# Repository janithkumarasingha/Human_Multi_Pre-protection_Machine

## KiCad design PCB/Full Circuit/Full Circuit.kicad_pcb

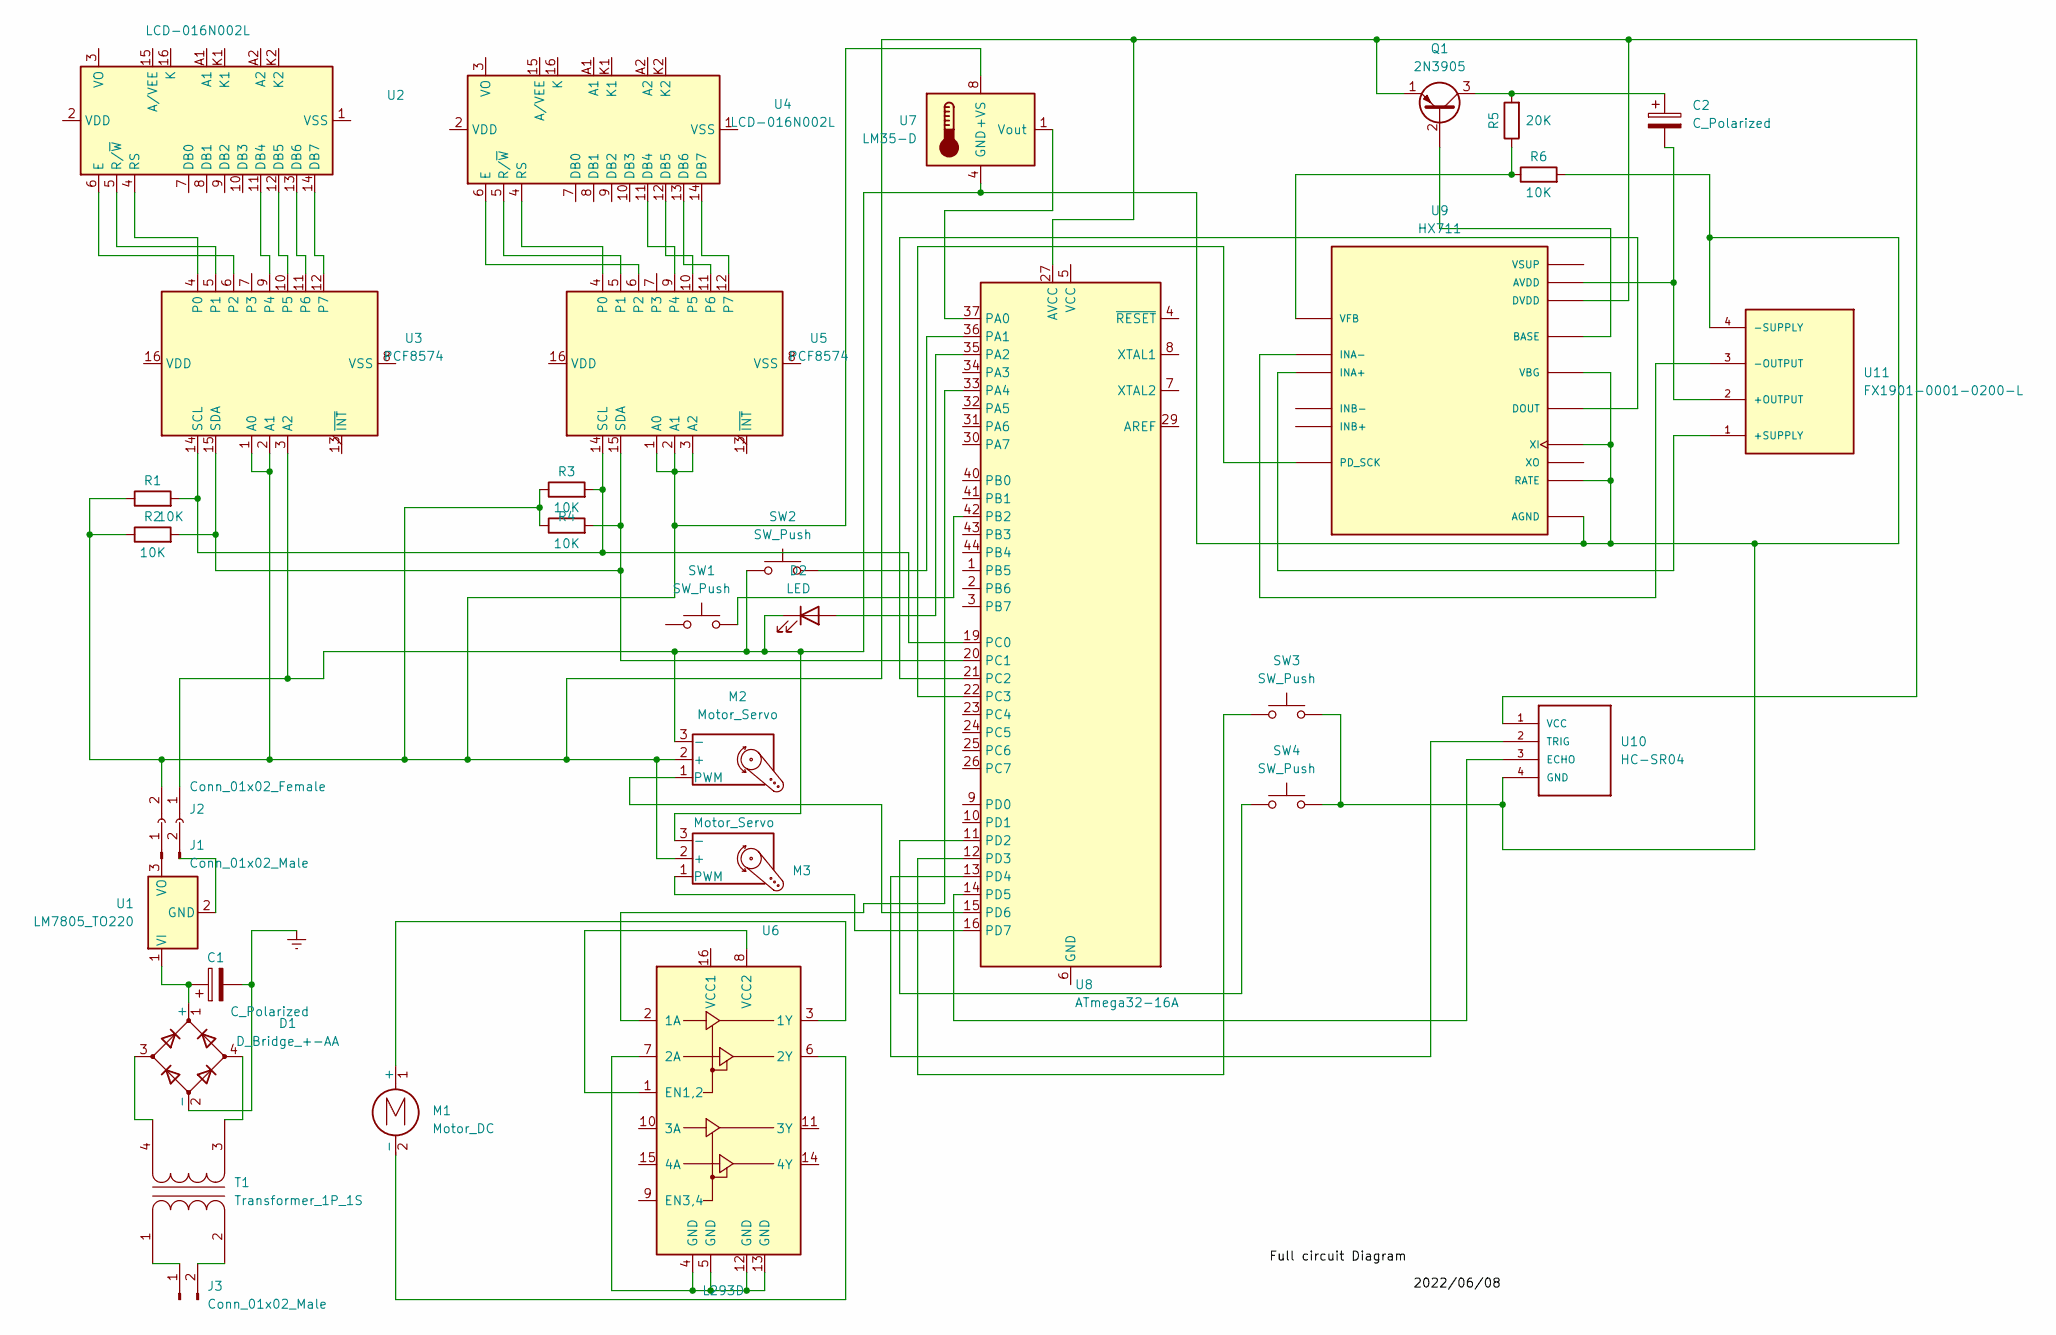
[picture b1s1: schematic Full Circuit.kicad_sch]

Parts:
C1, C2: C_Polarized; CP_Axial_L18.0mm_D10.0mm_P25.00mm_Horizontal
D1: D_Bridge_+-AA; Diode_Bridge_Round_D9.0mm
D2: LED; LED_D5.0mm_Horizontal_O1.27mm_Z3.0mm_IRBlack
J1, J3: Conn_01x02_Male; Stocko_MKS_1651-6-0-202_1x2_P2.50mm_Vertical
J2: Conn_01x02_Female; Stocko_MKS_1652-6-0-202_1x2_P2.50mm_Vertical
M1: Motor_DC; XDCR_C0720B001F
M2, M3: Motor_Servo; TO92254P520H877-3
Q1: 2N3905; TO-92_Inline
R1, R2, R3, R4, R6: 10K; R_Axial_DIN0414_L11.9mm_D4.5mm_P15.24mm_Horizontal
R5: 20K; R_Axial_DIN0414_L11.9mm_D4.5mm_P15.24mm_Horizontal
SW1, SW2, SW3, SW4: SW_Push; SW_PB400EEQX
T1: Transformer_1P_1S; Transformer_37x44
U1: LM7805_TO220; TO-220-3_Vertical
U2, U4: LCD-016N002L
U3, U5: PCF8574; DIP794W45P254L1969H508Q16
U6: L293D; DIP-16_W7.62mm
U7: LM35-D; SOIC-8_3.9x4.9mm_P1.27mm
U8: ATmega32-16A; TQFP-44_10x10mm_P0.8mm
U9: HX711; SOP127P600X180-16N; PARTREV V2.0
U10: HC-SR04; XCVR_HC-SR04
U11: FX1901-0001-0200-L; SENSOR_FX1901-0001-0200-L

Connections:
Earth: C1.2, D1.2 (-)
unnamed: C1.1, D1.1 (+), U1.1 (VI)
unnamed: C2.1, Q1.3 (C), R5.2
unnamed: C2.2, U9.3 (AVDD), U11.2 (+OUTPUT)
unnamed: D1.3, T1.4 (SB)
unnamed: D1.4, T1.3 (SA)
unnamed: D2.1 (K), J2.1, M2.3 (-), M3.3 (-), R6.2, SW2.1, SW3.2, SW4.2, U3.3 (A2), U7.4 (GND), U9.5 (AGND), U9.6 (VBG), U9.14 (XI), U9.15 (RATE), U10.4 (GND), U11.4 (-SUPPLY)
unnamed: D2.2 (A), U8.35 (PA2)
unnamed: J2.2, M2.2 (+), M3.2 (+), Q1.1 (E), R1.1, R2.1, R3.1, R4.1, U3.1 (A0), U3.2 (A1), U5.1 (A0), U5.2 (A1), U5.3 (A2), U7.8 (+VS), U8.27 (AVCC), U9.16 (DVDD), U10.1 (VCC)
unnamed: J3.1, T1.1 (AA)
unnamed: J3.2, T1.2 (AB)
unnamed: M1.1 (+), U6.3 (1Y)
unnamed: M1.2 (-), U6.6 (2Y)
unnamed: M2.1 (PWM), U8.15 (PD6)
unnamed: M3.1 (PWM), U8.16 (PD7)
unnamed: Q1.2 (B), U9.2 (BASE)
unnamed: R1.2, R3.2, U3.14 (SCL), U5.14 (SCL), U8.19 (PC0)
unnamed: R2.2, R4.2, U3.15 (SDA), U5.15 (SDA), U8.20 (PC1)
unnamed: R5.1, R6.1, U9.4 (VFB)
unnamed: SW1.2, U8.42 (PB2)
unnamed: SW2.2, U8.36 (PA1)
unnamed: SW3.1, U8.12 (PD3)
unnamed: SW4.1, U8.11 (PD2)
unnamed: U2.4 (RS), U3.4 (P0)
unnamed: U2.5 (R/~W), U3.5 (P1)
unnamed: U2.6 (E), U3.6 (P2)
unnamed: U2.11 (DB4), U3.9 (P4)
unnamed: U2.12 (DB5), U3.10 (P5)
unnamed: U2.13 (DB6), U3.11 (P6)
unnamed: U2.14 (DB7), U3.12 (P7)
unnamed: U4.4 (RS), U5.4 (P0)
unnamed: U4.5 (R/~W), U5.5 (P1)
unnamed: U4.6 (E), U5.6 (P2)
unnamed: U4.11 (DB4), U5.9 (P4)
unnamed: U4.12 (DB5), U5.10 (P5)
unnamed: U4.13 (DB6), U5.11 (P6)
unnamed: U4.14 (DB7), U5.12 (P7)
unnamed: U6.1 (EN1,2), U6.8 (VCC2)
unnamed: U6.2 (1A), U8.33 (PA4)
unnamed: U6.4 (GND), U6.5 (GND), U6.7 (2A), U6.12 (GND), U6.13 (GND)
unnamed: U7.1 (Vout), U8.37 (PA0)
unnamed: U8.5 (VCC), U8.17 (VCC), U8.38 (VCC)
unnamed: U8.6 (GND), U8.18 (GND), U8.28 (GND), U8.39 (GND)
unnamed: U8.21 (PC2), U9.12 (DOUT)
unnamed: U8.22 (PC3), U9.11 (PD_SCK)
unnamed: U8.13 (PD4), U10.2 (TRIG)
unnamed: U8.14 (PD5), U10.3 (ECHO)
unnamed: U9.8 (INA+), U11.1 (+SUPPLY)
unnamed: U9.7 (INA-), U11.3 (-OUTPUT)

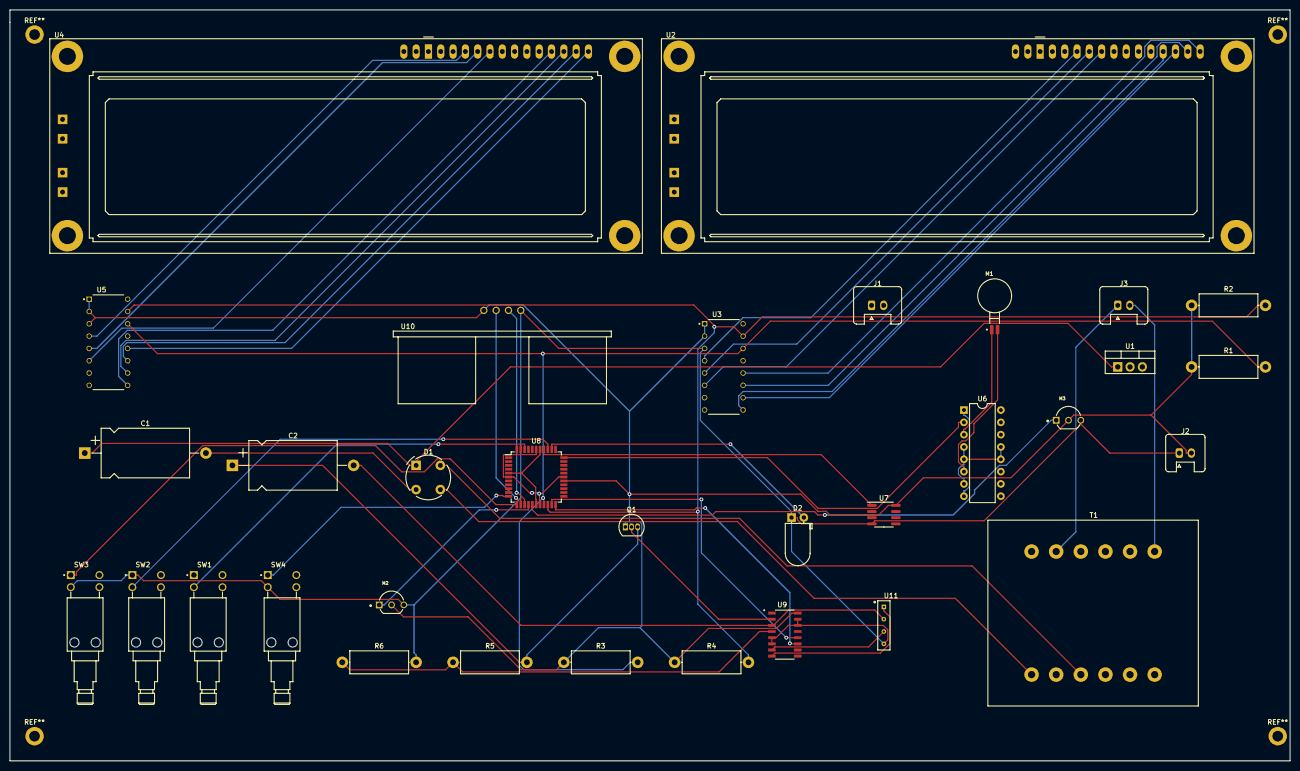
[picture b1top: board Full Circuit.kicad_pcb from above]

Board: 2 copper layers, 264.2 x 154.9 mm, 33 parts (0 on the bottom side), 49 nets.

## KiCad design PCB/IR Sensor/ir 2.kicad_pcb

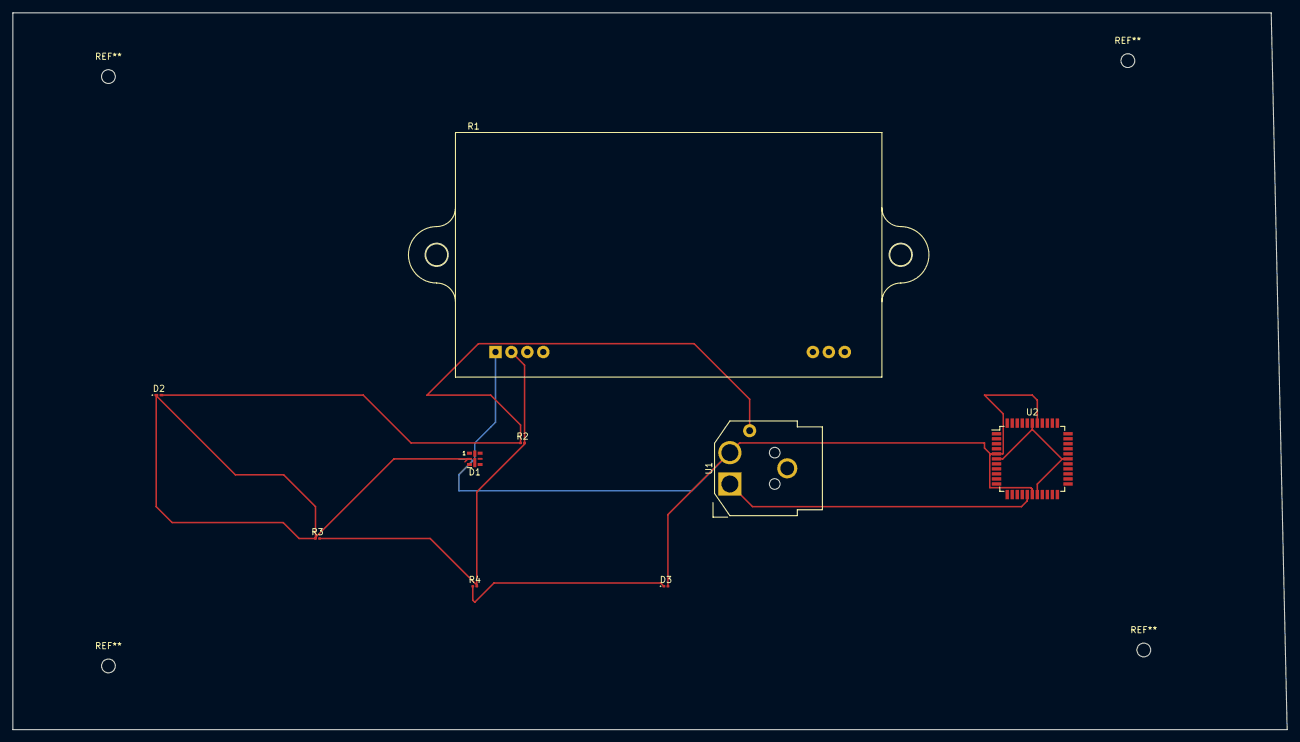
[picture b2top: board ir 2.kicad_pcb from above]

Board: 2 copper layers, 203.2 x 114.3 mm, 9 parts (0 on the bottom side), 7 nets.

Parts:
D1: LED; LED-APA102-2020
D2: D_Photo; D_0201_0603Metric_Pad0.64x0.40mm_HandSolder
D3: D_Photo; D_0201_0603Metric
R1: 150; Reverb_BTDR-1H
R2: 210000; R_0201_0603Metric
R3: 310000; R_0201_0603Metric
R4: 4150; R_0201_0603Metric
U1: LM358; CUI_PD-30
U2: ATmega32-16A; TQFP-44_10x10mm_P0.8mm

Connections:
unnamed: D1.1 (K), R1.1
unnamed: D2.2 (A), R2.1, U1.3 (+)
unnamed: D3.1 (K), R4.1
unnamed: R1.2, R2.2, R3.2, R4.2
unnamed: U1.1, U2.16 (PD7)
unnamed: U2.6 (GND), U2.18 (GND), U2.28 (GND), U2.39 (GND)
VCC: D1.2 (A), D2.1 (K), D3.2 (A), R3.1, U1.2 (-), U2.5 (VCC), U2.17 (VCC), U2.38 (VCC)

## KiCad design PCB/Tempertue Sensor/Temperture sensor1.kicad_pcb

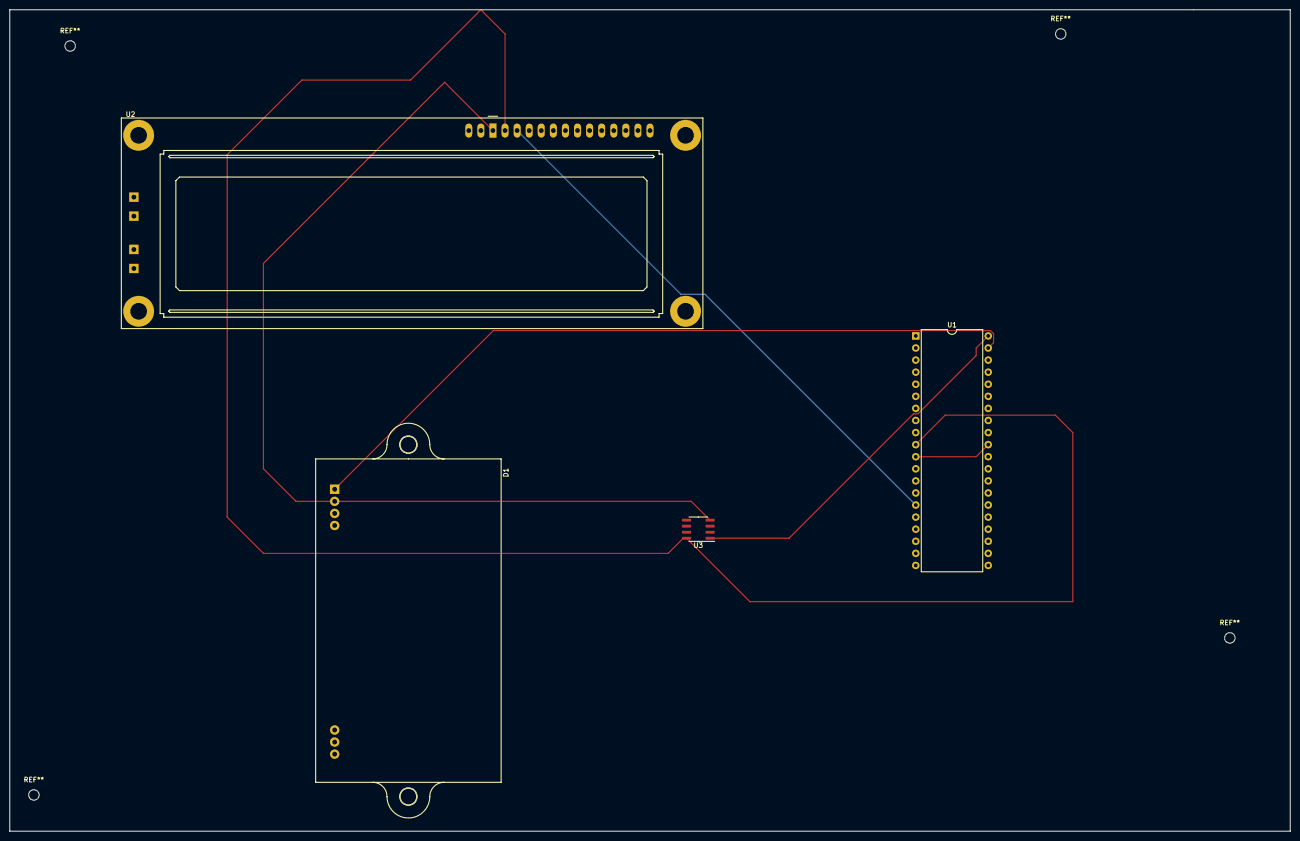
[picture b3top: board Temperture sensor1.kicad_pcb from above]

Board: 2 copper layers, 269.2 x 172.7 mm, 4 parts (0 on the bottom side), 6 nets.

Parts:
D1: LED; Reverb_BTDR-1H
U1: ATmega32A-P; DIP-40_W15.24mm
U2: LCD-016N002L
U3: LM35-D; SOIC-8_3.9x4.9mm_P1.27mm

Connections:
GNDD: D1.2 (A), U2.1 (VSS), U3.4 (GND)
unnamed: D1.1 (K), U1.39 (PA1)
unnamed: U1.11 (GND), U1.31 (GND)
unnamed: U1.15 (PD1), U2.3 (VO)
unnamed: U1.40 (PA0), U3.1 (Vout)
VCC: U1.10 (VCC), U2.2 (VDD), U3.8 (+VS)

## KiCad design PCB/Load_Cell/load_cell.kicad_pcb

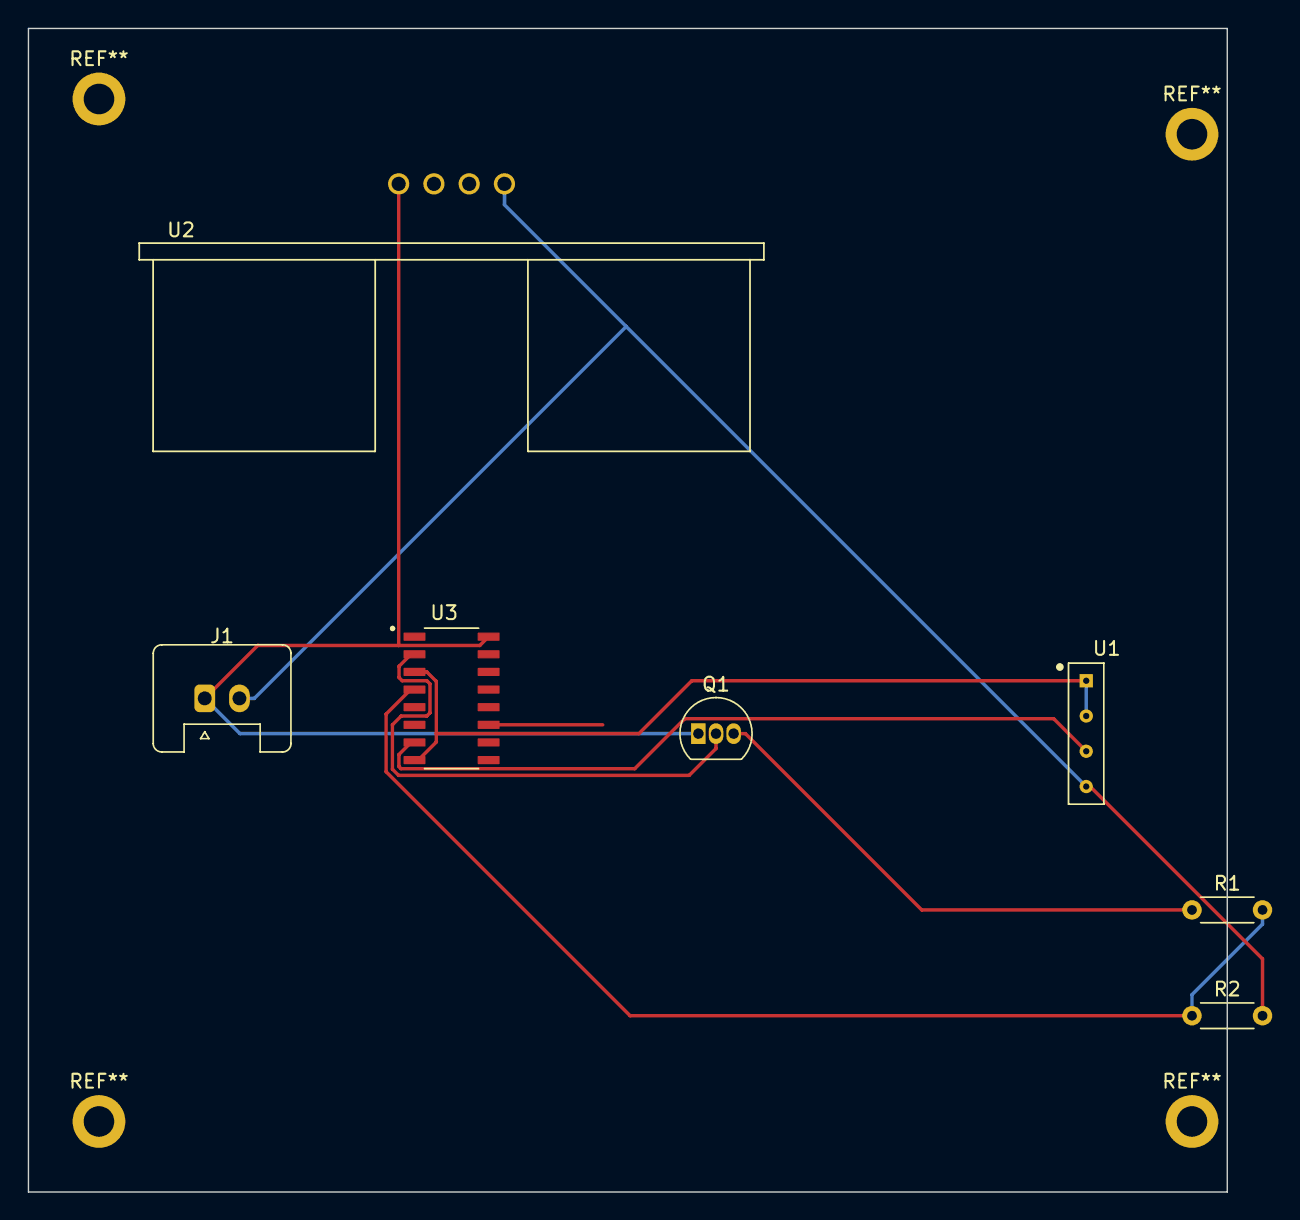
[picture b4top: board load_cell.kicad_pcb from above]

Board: 2 copper layers, 86.4 x 83.8 mm, 7 parts (0 on the bottom side), 7 nets.

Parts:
J1: Conn_01x02_Female; Stocko_MKS_1651-6-0-202_1x2_P2.50mm_Vertical
Q1: 2N3905; TO-92_Inline
R1, R2: R; R_Axial_DIN0204_L3.6mm_D1.6mm_P5.08mm_Horizontal
U1: FX1901-0001-0200-L; SENSOR_FX1901-0001-0200-L
U2: HC-SR04; XCVR_HC-SR04
U3: HX711; SOP127P600X180-16N

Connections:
unnamed: J1.1, Q1.1 (E), U2.1 (VCC), U3.16 (DVDD)
unnamed: J1.2, R2.2, U1.4 (-SUPPLY), U2.4 (GND)
unnamed: Q1.2 (B), U3.2 (BASE)
unnamed: Q1.3 (C), R1.1
unnamed: R1.2, R2.1, U3.4 (VFB)
unnamed: U1.1 (+SUPPLY), U1.2 (+OUTPUT), U3.3 (AVDD), U3.8 (INA+)
unnamed: U1.3 (-OUTPUT), U3.7 (INA-)

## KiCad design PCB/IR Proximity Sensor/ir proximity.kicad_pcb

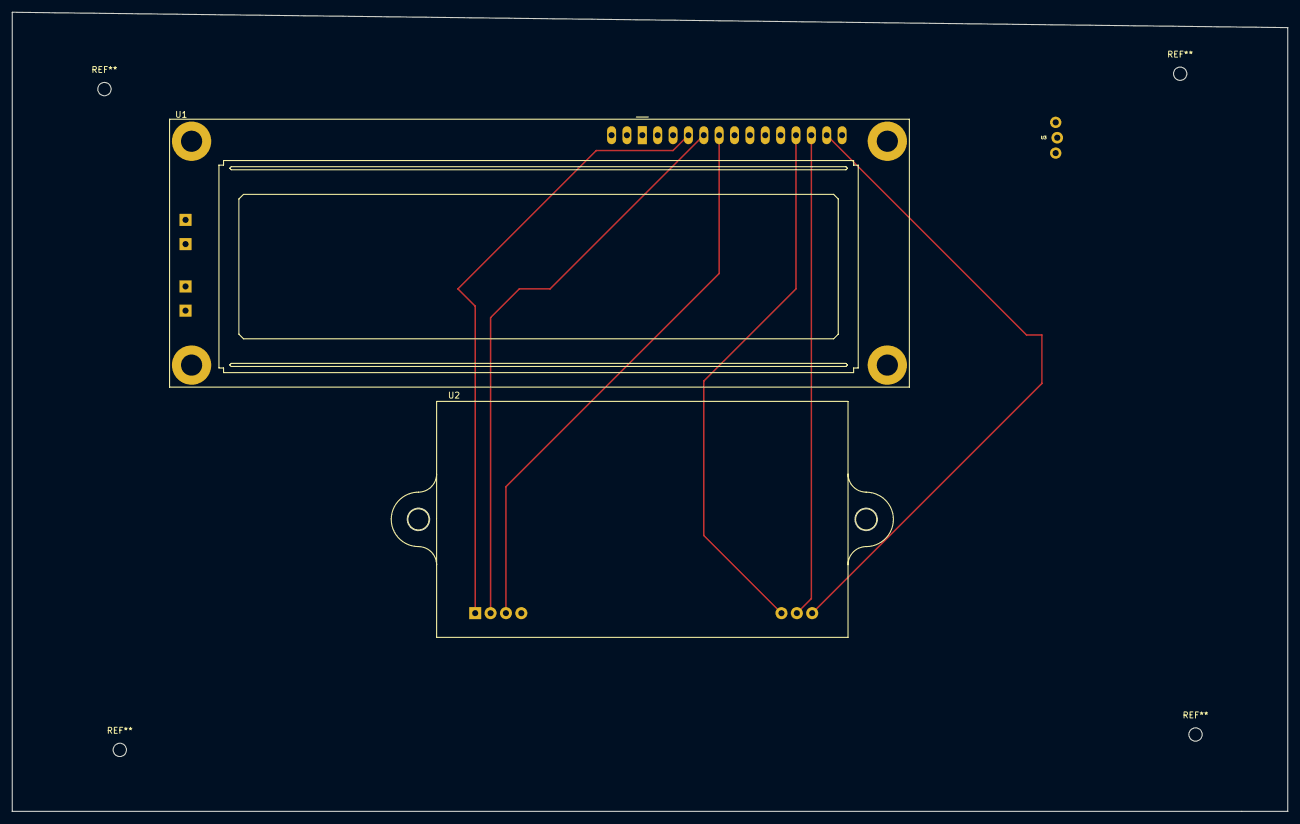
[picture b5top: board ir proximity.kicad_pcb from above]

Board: 2 copper layers, 210.8 x 132.1 mm, 3 parts (0 on the bottom side), 6 nets.

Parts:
U1: LCD-016N002L
U2: ATmega32A-P; Reverb_BTDR-1H
U3: TSSP58038

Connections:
unnamed: U1.4 (RS), U2.1 (PB0)
unnamed: U1.5 (R/~W), U2.2 (PB1)
unnamed: U1.6 (E), U2.3 (PB2)
unnamed: U1.11 (DB4), U2.5 (PB4)
unnamed: U1.12 (DB5), U2.6 (PB5)
unnamed: U1.13 (DB6), U2.7 (PB6)

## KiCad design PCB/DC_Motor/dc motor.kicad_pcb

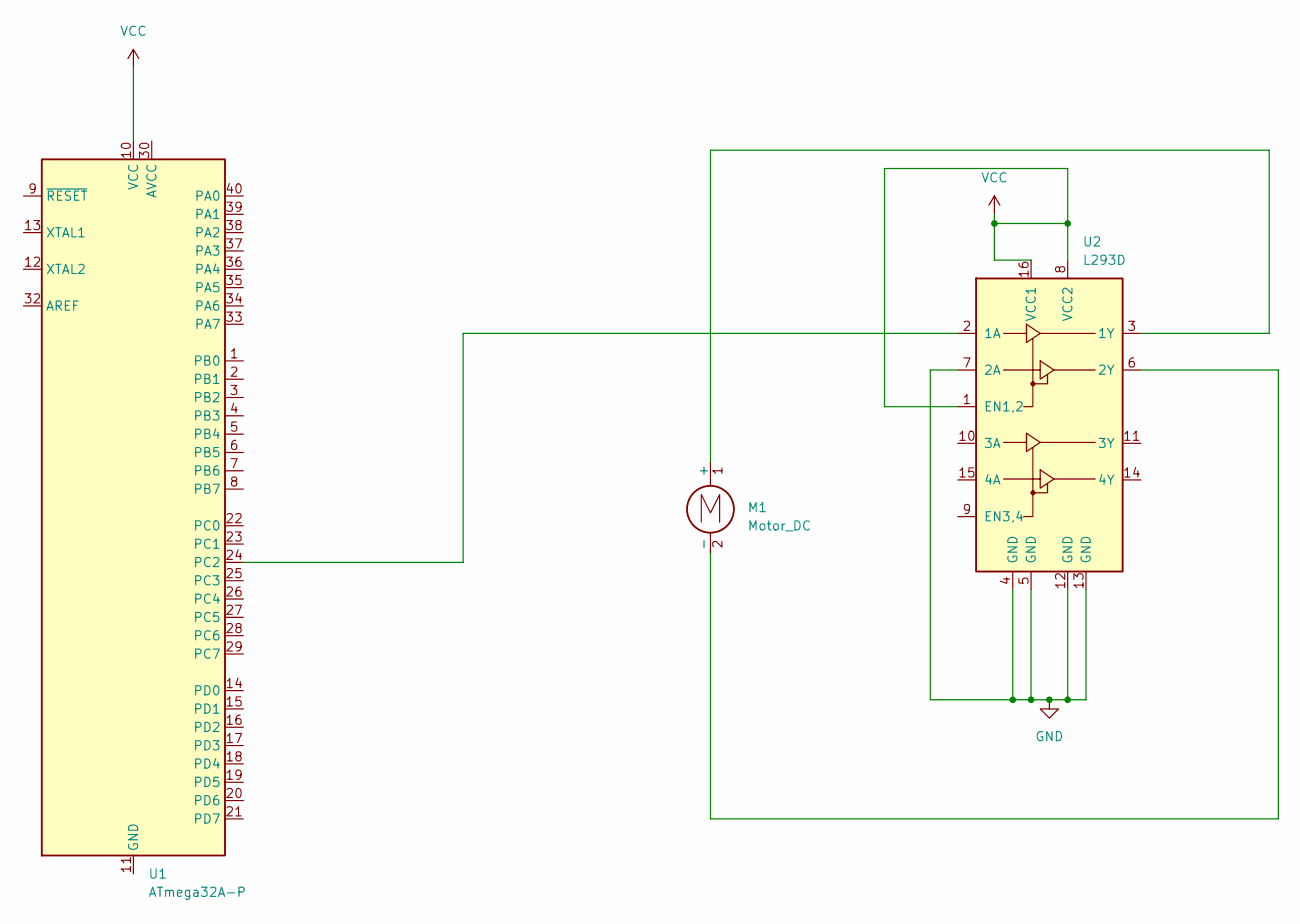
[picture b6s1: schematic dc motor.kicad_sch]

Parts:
M1: Motor_DC
U1: ATmega32A-P; DIP-40_W15.24mm
U2: L293D; DIP-16_W7.62mm

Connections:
GND: U2.4 (GND), U2.5 (GND), U2.7 (2A), U2.12 (GND), U2.13 (GND)
unnamed: M1.1 (+), U2.3 (1Y)
unnamed: M1.2 (-), U2.6 (2Y)
unnamed: U1.11 (GND), U1.31 (GND)
unnamed: U1.24 (PC2), U2.2 (1A)
VCC: U1.10 (VCC), U2.1 (EN1,2), U2.8 (VCC2), U2.16 (VCC1)

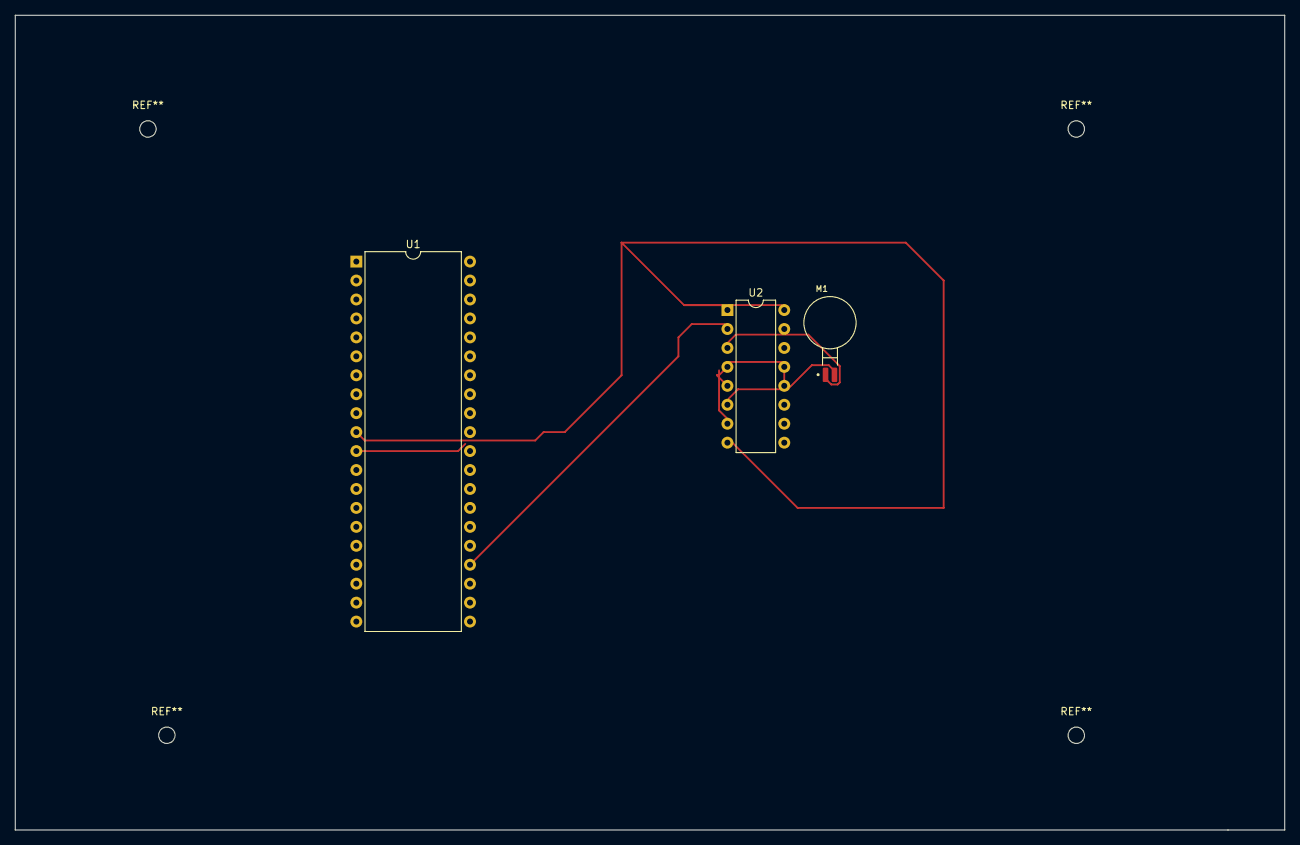
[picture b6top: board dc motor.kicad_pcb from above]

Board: 2 copper layers, 170.2 x 109.2 mm, 3 parts (0 on the bottom side), 6 nets.

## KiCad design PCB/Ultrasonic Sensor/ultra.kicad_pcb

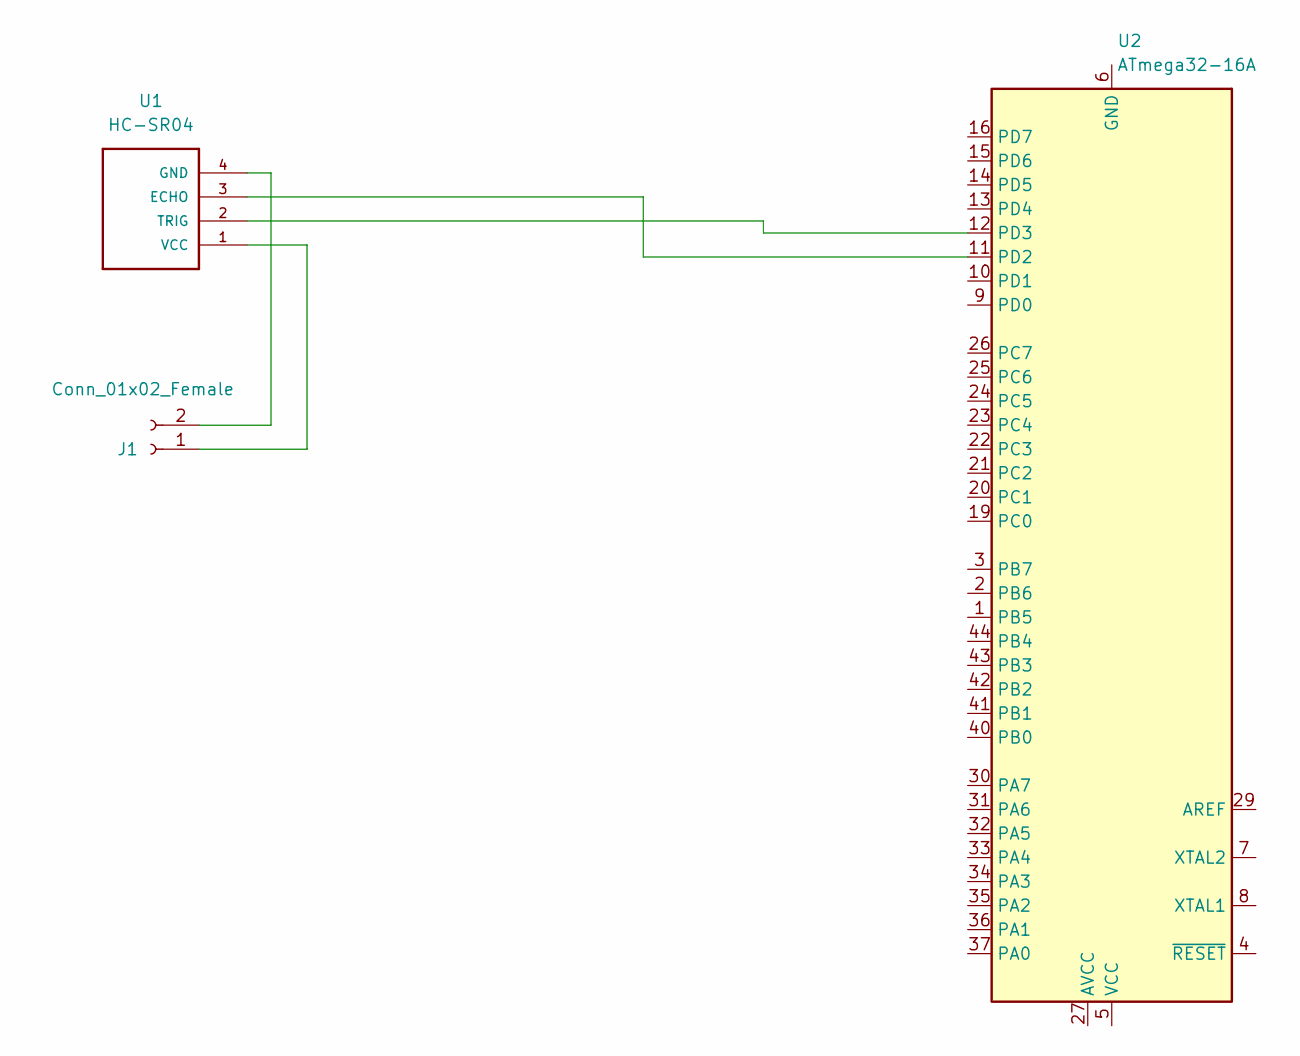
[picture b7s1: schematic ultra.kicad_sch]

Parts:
J1: Conn_01x02_Female; Stocko_MKS_1652-6-0-202_1x2_P2.50mm_Vertical
U1: HC-SR04; XCVR_HC-SR04
U2: ATmega32-16A; TQFP-44_10x10mm_P0.8mm

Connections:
unnamed: J1.1, U1.1 (VCC)
unnamed: J1.2, U1.4 (GND)
unnamed: U1.2 (TRIG), U2.12 (PD3)
unnamed: U1.3 (ECHO), U2.11 (PD2)
unnamed: U2.5 (VCC), U2.17 (VCC), U2.38 (VCC)
unnamed: U2.6 (GND), U2.18 (GND), U2.28 (GND), U2.39 (GND)

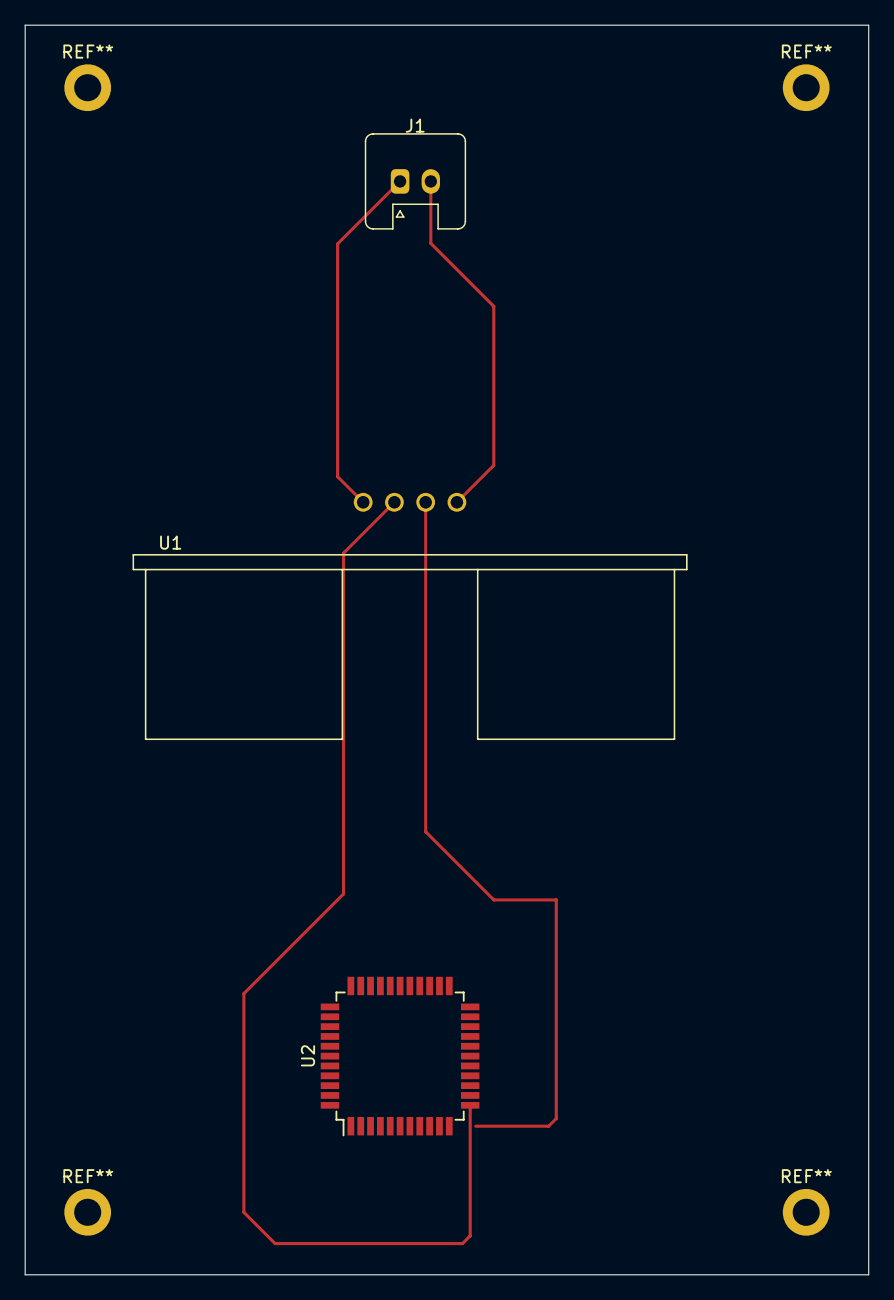
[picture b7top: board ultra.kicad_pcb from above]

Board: 2 copper layers, 68.6 x 101.6 mm, 3 parts (0 on the bottom side), 6 nets.

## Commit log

2023-06-08 complet project
2023-06-08 header file LCDI2C.h
2023-06-08 I2C.h
2023-06-08 .vscode
2023-06-08 debug commit
2023-06-08 Add files via upload
    power supply
2023-06-08 PCB
    PCB
